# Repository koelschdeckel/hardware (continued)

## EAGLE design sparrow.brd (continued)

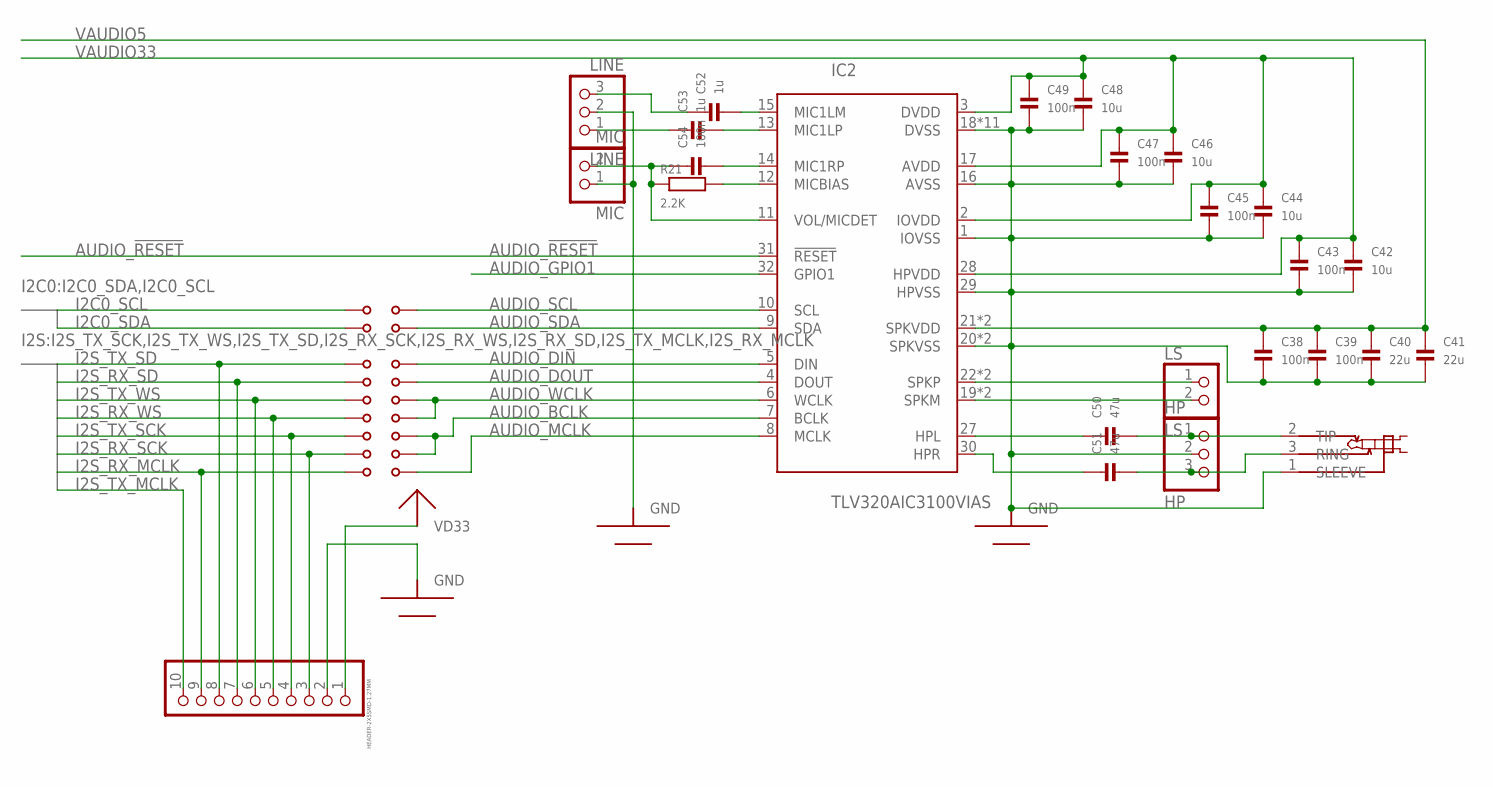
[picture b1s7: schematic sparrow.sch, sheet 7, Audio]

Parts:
A_SCL: JUMPERSOLDER_CLOSED; 0603_SOLDERJUMPER_CLOSED
A_SDA: JUMPERSOLDER_CLOSED; 0603_SOLDERJUMPER_CLOSED
C38, C39, C43, C45, C47, C49, C54: 100n; 0603
C40, C41: 22u; 0603
C42, C44, C46, C48: 10u; 0603
C50, C51: 47u; 0805
C52, C53: 1u; 0603
HEADPHONE: AUDIOJACK-STEREO-3PCUI_SJ_3523; CUI_SJ_3523_SMT
HP: HP; 1X03_ROUND
I2S: HEADER-2X5SMD-1.27MM; 2X05_SMT
IC2: TLV320AIC3100VIAS; QFN32-0.5-EP-VIAS
LINE: LINE; 1X03_ROUND
LS: LS; 1X02_ROUND
MCLK: JUMPERSOLDER_CLOSED; 0603_SOLDERJUMPER_CLOSED
MIC: MIC; 1X02_ROUND
R21: 2.2K; 0603
RX_SCK: JUMPERSOLDER_CLOSED; 0603_SOLDERJUMPER_CLOSED
RX_SD: JUMPERSOLDER_CLOSED; 0603_SOLDERJUMPER_CLOSED
RX_WS: JUMPERSOLDER_CLOSED; 0603_SOLDERJUMPER_CLOSED
TX_SCK: JUMPERSOLDER_CLOSED; 0603_SOLDERJUMPER_CLOSED
TX_SD: JUMPERSOLDER_CLOSED; 0603_SOLDERJUMPER_CLOSED
TX_WS: JUMPERSOLDER_CLOSED; 0603_SOLDERJUMPER_CLOSED

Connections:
AUDIO_!RESET: IC2.31 (!RESET); also elsewhere on the board
AUDIO_BCLK: IC2.7 (BCLK), RX_SCK.2, TX_SCK.2
AUDIO_DIN: IC2.5 (DIN), TX_SD.2
AUDIO_DOUT: IC2.4 (DOUT), RX_SD.2
AUDIO_GPIO1: IC2.32 (GPIO1)
AUDIO_MCLK: IC2.8 (MCLK), MCLK.2
AUDIO_SCL: A_SCL.2, IC2.10 (SCL)
AUDIO_SDA: A_SDA.2, IC2.9 (SDA)
AUDIO_WCLK: IC2.6 (WCLK), RX_WS.2, TX_WS.2
GND: C38.2, C39.2, C40.2, C41.2, C42.2, C43.2, C44.2, C45.2, C46.2, C47.2, C48.2, C49.2, HEADPHONE.1 (SLEEVE), HP.2, I2S.2, IC2.1 (IOVSS), IC2.16 (AVSS), IC2.18 (DVSS), IC2.20 (SPKVSS), IC2.25 (SPKVSS), IC2.29 (HPVSS), IC2.PAD (DVSS), IC2.VIA1 (DVSS), IC2.VIA2 (DVSS), IC2.VIA3 (DVSS), IC2.VIA4 (DVSS), IC2.VIA5 (DVSS), IC2.VIA6 (DVSS), IC2.VIA7 (DVSS), IC2.VIA8 (DVSS), IC2.VIA9 (DVSS), LINE.2, MIC.1; also elsewhere on the board
HPL: C50.1, IC2.27 (HPL)
HPR: C51.1, IC2.30 (HPR)
HP_L: C50.2, HEADPHONE.2 (TIP), HP.1
HP_R: C51.2, HEADPHONE.3 (RING), HP.3
I2C0_SCL: A_SCL.1; also elsewhere on the board
I2C0_SDA: A_SDA.1; also elsewhere on the board
I2S_RX_MCLK: I2S.9, MCLK.1; also elsewhere on the board
I2S_RX_SCK: I2S.3, RX_SCK.1; also elsewhere on the board
I2S_RX_SD: I2S.7, RX_SD.1; also elsewhere on the board
I2S_RX_WS: I2S.5, RX_WS.1; also elsewhere on the board
I2S_TX_MCLK: I2S.10; also elsewhere on the board
I2S_TX_SCK: I2S.4, TX_SCK.1; also elsewhere on the board
I2S_TX_SD: I2S.8, TX_SD.1; also elsewhere on the board
I2S_TX_WS: I2S.6, TX_WS.1; also elsewhere on the board
LINEIN1: C52.1, LINE.3
LINEIN2: C53.1, LINE.1
MIC1LM: C52.2, IC2.15 (MIC1LM)
MIC1LP: C53.2, IC2.13 (MIC1LP)
MIC1RP: C54.2, IC2.14 (MIC1RP)
MICBIAS: IC2.12 (MICBIAS), R21.2
unnamed: C54.1, IC2.11 (VOL/MICDET), MIC.2, R21.1
SPKM: IC2.19 (SPKM), IC2.23 (SPKM), LS.2
SPKP: IC2.22 (SPKP), IC2.26 (SPKP), LS.1
VAUDIO5: C38.1, C39.1, C40.1, C41.1, IC2.21 (SPKVDD), IC2.24 (SPKVDD); also elsewhere on the board
VAUDIO33: C42.1, C43.1, C44.1, C45.1, C46.1, C47.1, C48.1, C49.1, IC2.2 (IOVDD), IC2.3 (DVDD), IC2.17 (AVDD), IC2.28 (HPVDD); also elsewhere on the board
VD33: I2S.1; also elsewhere on the board

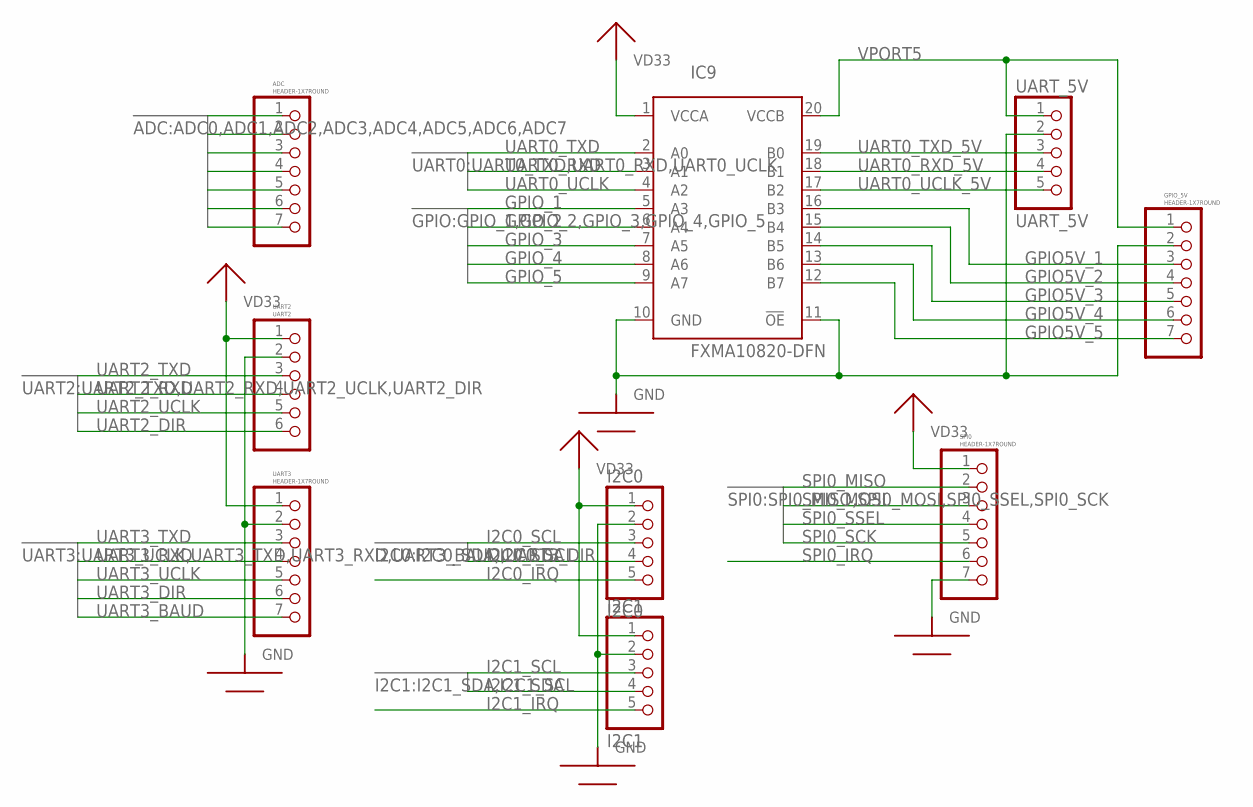
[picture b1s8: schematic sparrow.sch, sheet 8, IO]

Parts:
ADC: HEADER-1X7ROUND; 1X07_ROUND
GPIO_5V: HEADER-1X7ROUND; 1X07_ROUND
I2C0: I2C0; 1X05_ROUND
I2C1: I2C1; 1X05_ROUND
IC9: FXMA10820-DFN; FXMA108
SPI0: HEADER-1X7ROUND; 1X07_ROUND
UART2: UART2; 1X06_ROUND
UART3: HEADER-1X7ROUND; 1X07_ROUND
UART_5V: UART_5V; 1X05_ROUND

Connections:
ADC0: ADC.1; also elsewhere on the board
ADC1: ADC.2; also elsewhere on the board
ADC2: ADC.3; also elsewhere on the board
ADC3: ADC.4; also elsewhere on the board
ADC4: ADC.5; also elsewhere on the board
ADC5: ADC.6; also elsewhere on the board
ADC6: ADC.7; also elsewhere on the board
GND: GPIO_5V.2, I2C0.2, I2C1.2, IC9.10 (GND), IC9.11 (!OE), SPI0.7, UART2.2, UART3.2, UART_5V.2; also elsewhere on the board
GPIO5V_1: GPIO_5V.3, IC9.16 (B3)
GPIO5V_2: GPIO_5V.4, IC9.15 (B4)
GPIO5V_3: GPIO_5V.5, IC9.14 (B5)
GPIO5V_4: GPIO_5V.6, IC9.13 (B6)
GPIO5V_5: GPIO_5V.7, IC9.12 (B7)
GPIO_1: IC9.5 (A3); also elsewhere on the board
GPIO_2: IC9.6 (A4); also elsewhere on the board
GPIO_3: IC9.7 (A5); also elsewhere on the board
GPIO_4: IC9.8 (A6); also elsewhere on the board
GPIO_5: IC9.9 (A7); also elsewhere on the board
I2C0_IRQ: I2C0.5; also elsewhere on the board
I2C0_SCL: I2C0.3; also elsewhere on the board
I2C0_SDA: I2C0.4; also elsewhere on the board
I2C1_IRQ: I2C1.5; also elsewhere on the board
I2C1_SCL: I2C1.3; also elsewhere on the board
I2C1_SDA: I2C1.4; also elsewhere on the board
SPI0_IRQ: SPI0.6; also elsewhere on the board
SPI0_MISO: SPI0.2; also elsewhere on the board
SPI0_MOSI: SPI0.3; also elsewhere on the board
SPI0_SCK: SPI0.5; also elsewhere on the board
SPI0_SSEL: SPI0.4; also elsewhere on the board
UART0_RXD: IC9.3 (A1); also elsewhere on the board
UART0_RXD_5V: IC9.18 (B1), UART_5V.4
UART0_TXD: IC9.2 (A0); also elsewhere on the board
UART0_TXD_5V: IC9.19 (B0), UART_5V.3
UART0_UCLK: IC9.4 (A2); also elsewhere on the board
UART0_UCLK_5V: IC9.17 (B2), UART_5V.5
UART2_DIR: UART2.6; also elsewhere on the board
UART2_RXD: UART2.4; also elsewhere on the board
UART2_TXD: UART2.3; also elsewhere on the board
UART2_UCLK: UART2.5; also elsewhere on the board
UART3_BAUD: UART3.7; also elsewhere on the board
UART3_DIR: UART3.6; also elsewhere on the board
UART3_RXD: UART3.4; also elsewhere on the board
UART3_TXD: UART3.3; also elsewhere on the board
UART3_UCLK: UART3.5; also elsewhere on the board
VD33: I2C0.1, I2C1.1, IC9.1 (VCCA), SPI0.1, UART2.1, UART3.1; also elsewhere on the board
VPORT5: GPIO_5V.1, IC9.20 (VCCB), UART_5V.1; also elsewhere on the board

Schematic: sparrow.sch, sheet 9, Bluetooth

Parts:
ANT2: 2.4GHz 50Ω; 1206_MINIMELF_COMBO
BAL1: BALUNWLCSP; ST_BAL_WLCSP
C1: 1n; 0402
C61: 47n; 0402
C62, C63, C64: 100n; 0402
C66, C67: 12p; 0402
C68, C69: 9p; 0402
C72: 2.2n; 0402
MCU1: NRF51822QFN48; QFN48_EP
NRF_DEBUG: HEADER-2X5SMD-1.27MM; 2X05_SMT
R34: 100K; 0603
X3: 32768; 1206_MINIMELF_COMBO
X5: 16MHz; CRYSTAL25X20

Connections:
BT_ANT: ANT2.1, BAL1.SE (UNBAL)
BT_ANT1: BAL1.DIFF2 (BAL2), MCU1.31 (ANT1)
BT_ANT2: BAL1.DIFF1 (BAL1), MCU1.32 (ANT2)
BT_DEC1: C62.P$1, MCU1.39 (DEC1)
BT_DEC2: C61.P$1, MCU1.29 (DEC2)
BT_VDD_PA: BAL1.VCC (DC), C72.P$2, MCU1.30 (VDD_PA)
BT_XC1: C67.P$1, MCU1.37 (XC1), X5.1
BT_XC2: C66.P$1, MCU1.38 (XC2), X5.3 (2)
BT_XL1: C69.P$2, MCU1.46 (P0.27), X3.1
BT_XL2: C68.P$2, MCU1.45 (P0.26), X3.2
GND: BAL1.GND, C1.P$2, C61.P$2, C62.P$2, C63.P$2, C64.P$2, C66.P$2, C67.P$2, C68.P$1, C69.P$1, C72.P$1, MCU1.13 (VSS), MCU1.33 (VSS), MCU1.34 (VSS), MCU1.PAD (VSS), NRF_DEBUG.3, NRF_DEBUG.5, NRF_DEBUG.7, NRF_DEBUG.9, R34.1, X5.2 (GND), X5.4 (GND); also elsewhere on the board
NRF_SWDCLK: MCU1.24 (SWDCLK), NRF_DEBUG.4, R34.2; also elsewhere on the board
NRF_SWDIO: MCU1.23 (SWDIO/NRESET), NRF_DEBUG.2; also elsewhere on the board
UART1_CTS: MCU1.7 (P0.03); also elsewhere on the board
UART1_RTS: MCU1.6 (P0.02); also elsewhere on the board
UART1_RXD: MCU1.5 (P0.01); also elsewhere on the board
UART1_TXD: MCU1.4 (P0.00); also elsewhere on the board
VD33: C1.P$1, C63.P$1, C64.P$1, MCU1.1 (VDD), MCU1.12 (VDD), MCU1.35 (AVDD), MCU1.36 (AVDD), NRF_DEBUG.1; also elsewhere on the board

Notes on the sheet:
Note: R34 only needed for first revision of NRF51822. DNP for Rev. 2 and up.

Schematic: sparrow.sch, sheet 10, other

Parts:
LOGO2, LOGO3, LOGO4: LOGOKRONE; LOGO-KRONE

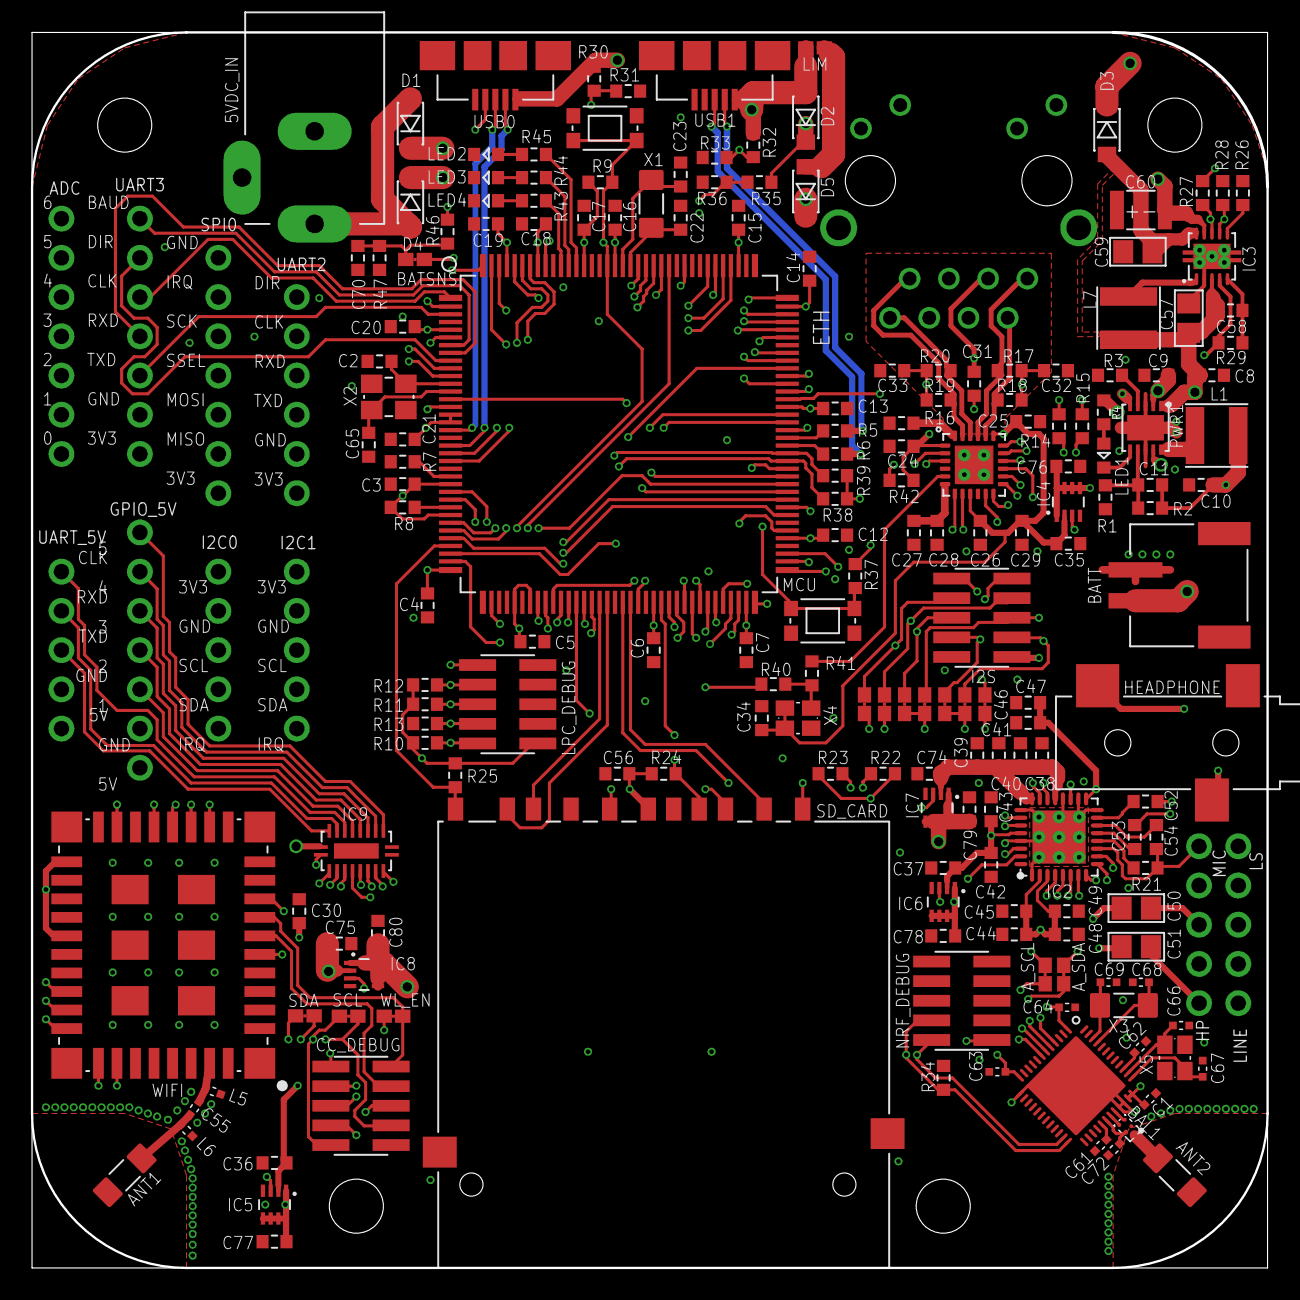
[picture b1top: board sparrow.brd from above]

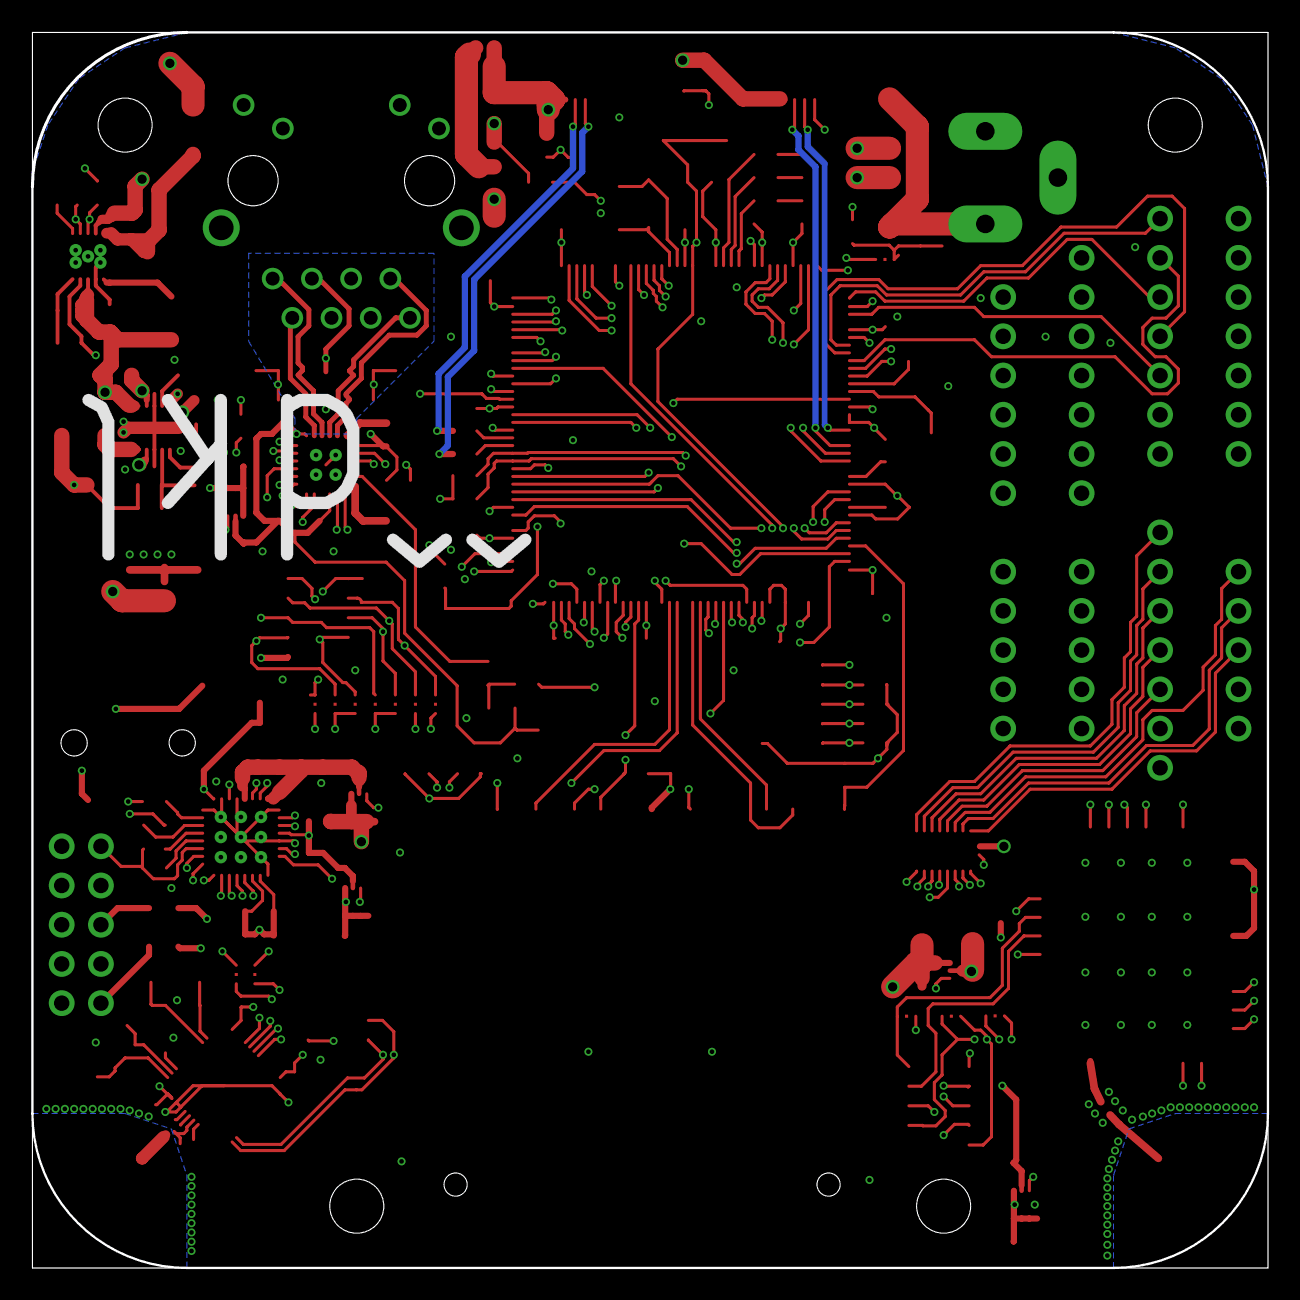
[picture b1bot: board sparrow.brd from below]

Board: 4 copper layers, 80.0 x 80.0 mm, 201 parts (3 on the bottom side), 193 nets.

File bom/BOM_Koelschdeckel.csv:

,BOM #,# Sparrow,Parts sparrow,Type,Value,Shape,Manuf,Model,Alt,Mouser #,DK #
,,,,,,,,,,,
Resistors,,,,,,,,,,,
,1,4,"R5, R6, R40, R41",Resistor,33Ω 1%,0603,Samsung,RC1608F330CS,"Vishay CRCW060333R0FKEA, Rohm MCR03ERTF33R0",71-CRCW0603-33-E3,1276-4524-1-ND
,2,4,"R17, R18, R19, R20",Resistor,49.9Ω 1%,0603,Samsung,RC1608F49R9CS,Vishay CRCW060349R9FKEA,71-CRCW0603-49.9-E3,1276-3505-1-ND
,3,2,"R14, R15",Resistor,330Ω,0603,Samsung,RC1608J331CS,"Yageo RC0603JR-07330RL, Yageo AF0603FR-07330RL, Vishay CRCW0603330RFKEA ",71-CRCW0603-330-E3,311-330GRCT-ND
,4,1,R3,Resistor,806Ω,0603,Yageo,RC0603FR-07806RL,KOA RK73H1JTTD8060F,660-RK73H1JTTD8060F,311-806HRCT-ND
,5,4,"R4, R43, R44, R45",Resistor,1K,0603,Samsung,RC1608J102CS,"Vishay CRCW06031K00FKEA, KOA RK73H1JTTD1001F",660-RK73H1JTTD1001F,1276-5062-1-ND
,6,5,"R21, R22, R23, R38, R39",Resistor,2.2K,0603,Samsung,RC1608J222CS,"KOA RK73H1JTTD2201F, Vishay CRCW06032K20FKEA, Yageo RC0603JR-072K2L",660-RK73H1JTTD2201F,1276-5070-1-ND
,7,9,"R30, R32, R42, R8, R9, R10, R11, R12, R13",Resistor,10K,0603,Samsung,RC1608J103CS,"Yageo RC0603JR-0710KL, Voshay CRCW060310K0FKEA, KOA RK73H1JTTD1002F",660-RK73H1JTTD1002F,1276-5086-1-ND
,8,1,R7,Resistor,12K 1%,0603,Samsung,RC1608F123CS,"Rohm MCR03ERTF1202, KOA RK73H1JTTD1212F, Vishay CRCW060312K1FKEA",660-RK73H1JTTD1212F,1276-4750-1-ND
,9,1,R16,Resistor,12.1K 1%,0603,Samsung,RC1608F1212CS,"KOA RK73H1JTTD1212F, Vishay CRCW060312K1FKEA, Stackpole RMCF0603FT12K1",660-RK73H1JTTD1212F,1276-4751-1-ND
,10,1,R26,Resistor,40.2K,0603,Samsung,RC1608F4022CS,"Yageo RC0603FR-0740K2L, KOA RK73H1JTTD4022F, Vishay CRCW060340K2FKEB",660-RK73H1JTTD4022F,1276-4800-1-ND
,11,11,"R24, R25, R27, R28, R29, R31, R33, R34, R35, R36, R37",Resistor,100K,0603,Samsung,RC1608J104CS,"Yageo RC0603JR-07100KL, Vishay CRCW0603100KFKEA, KOA RK73H1JTTD1003F",660-RK73H1JTTD1003F,1276-5110-1-ND
,12,3,"R1, R46, R47",Resistor,768K,0603,Yageo,RC0603FR-07768KL,"KOA RK73H1JTTD7683F, Rohm MCR03ERTF7683, Vishay CRCW0603768KFKEA",660-RK73H1JTTD7683F,311-768KHRCT-ND
,13,1,R2,Resistor,2.4M,0603,Samsung,RC1608J245CS,"KOA RK73B1JTTD245J, Vishay CRCW06032M40JNEA, Yageo RC0603JR-072M4L",660-RK73B1JTTD245J,1276-5143-1-ND
Capacitors,,,,,,,,,,,
,14,1,C55,Capacitor,2.2p,0402,Samsung,CL05C2R2CB5NNNC,Johanson 500R07S2R2DV4T,609-500R07S2R2DV4T,1276-1271-1-ND
,15,2,"C68, C69",Capacitor,9p,0402,Samsung,CL05C090DB5NNNC,Murata GRM1555C1H9R0CA01D,81-GRM1555C1H9R0CA1D,1276-1617-1-ND
,16,,,Capacitor,9p,0603,Samsung,CL10C090DB8NNNC,TDK C1608C0G1H090C080AA,810-C1608C0G1H090C,1276-2143-1-ND
,17,1,C11,Capacitor,10p 5%,0603,Samsung,CL10C100JB8NCNC,Vishay VJ0603A100JXACW1BC,77-VJ0603A100JXACBC,1276-2154-1-ND
,18,2,"C66, C67",Capacitor,12p,0402,Samsung,CL05C120JB5NNNC,Johanson 500R07S120KV4T,609-500R07S120KV4T,1276-1178-1-ND 
,19,4,"C2, C22, C23, C65",Capacitor,18p 5%,0603,Samsung,CL10C180JC8NNNC,Vishay VJ0603A180JXACW1BC,77-VJ0603A180JXACBC,1276-2210-1-ND
,20,1,C28,Capacitor,470p 5%,0603,Samsung,CL10C471JB8NCNC,Vishay VJ0603A471JXXCW1BC,77-VJ0603A471JXXCBC,1276-2302-1-ND
,21,1,C1,Capacitor,1n,0402,Samsung,CL05B102KB5NCNC,KOA X7R0402HTTP102K,660-X7R0402HTTP102K,1276-1492-1-ND
,22,1,C72,Capacitor,2.2n,0402,Samsung,CL05B222KB5NNNC,Vishay VJ0402Y222KXJCW1BC,77-VJ0402Y222KXJCBC,1276-1054-1-ND
,23,3,"C24, C25, C26",Capacitor,10n, ,Samsung,CL10B103KB8NCNC,Vishay VJ0603Y103KXAAC,77-VJ0603Y103KXAAC,1276-1921-1-ND
,24,1,C61,Capacitor,47n,0402,Samsung,CL05B473KP5NNNC,Vishay VJ0402Y473KXQCW1BC,77-VJ0402Y473KXQCBC,1276-1573-1-ND
,25,3,"C62, C63, C64",Capacitor,100n,0402,Samsung,CL05A104KP5NNNC,Vishay VJ0402G104MXQPW1BC,77-VJ0402G104MXQPBC,1276-1022-1-ND
,26,34,"C3, C4, C5, C6, C7, C12, C13, C14, C15, C16, C17, C18. C19, C20, C21, C30, C31, C32, C33, C34, C35, C36, C37. C38, C39, C43, C45, C47, C49, C54, C58, C70, C74, C75",Capacitor,100n,0603,Samsung,CL10B104KO8NNNC,Vishay VJ0603Y104JXJPW1BC,77-VJ0603Y104JXJPBC,1276-1005-1-ND
,27,9,"C27, C52, C53, C56, C76, C77, C78, C79, C80",Capacitor,1u,0603,Samsung,CL10B105KP8NNNC,AVX 0603YD105KAT2A,581-0603YD105K,1276-1946-1-ND
,28,3,"C8, C9, C10",Capacitor,4.7u,0603,Samsung,CL10B475KQ8NQNC,Murata GRM188R60J475ME19D,81-GRM188R60J475ME9D,1276-2087-1-ND
,29,5,"C29, C42, C44, C46, C48",Capacitor,10u,0603,Samsung,CL10A106MQ8NNNC,AVX 06036D106MAT2A,581-06036D106MAT2A,1276-1119-1-ND
,30,2,"C40, C41",Capacitor,22u 6.3V,0603,Samsung,CL10A226MQ8NRNC,"Murata GRM188R60J226MEA0D, TDK C1608X5R0J226M080AC",810-C1608X5R0J226M,1276-1193-1-ND
,31,2,"C57, C59",Capacitor,22u 10V,0805,Samsung,CL21A226MPQNNNE,TDK C2012X5R1A226M125AB,810-C2012X5R1A226M-3,1276-2910-1-ND
,32,2,"C50, C51",Capacitor,47u 6.3V,0805,Samsung,CL21A476MQCLRNC,Taiyo Yuden JMK212BJ476MG-T,963-JMK212BJ476MG-T,1276-2420-1-ND
,33,1,C60,Capacitor,150u 10V,1210_POL,AVX,TLNT157M010R1500,AVX TLJB157M010R0500,581-TLNT157M010R,478-3349-1-ND
Inductors,,,,,,,,,,,
,34,1,L5,Inductor,2.2n,0402,Taiyo Yuden,HK10052N2S-T,"Taiyo Yuden HK10052N2S-T, Panasonic ELJ-RF2N2ZFB, TDK MLG1005S2N2S",963-HK10052N2S-T,587-1503-1-ND
,35,1,L7,Inductor,"2.2u 2.2Arms, 3A sat",40x40,Laird,TYS40302R2N-10,"Bourns SRN4018-2R2M, Taiyo Yuden NRS4018T2R2MDGJ",963-NRS4018T2R2MDGJ,240-2697-1-ND
,36,1,L1,Inductor,10u 1A,40x40,Taiyo Yuden,NRS4018T100MDGJ,,963-NRS4018T100MDGJ,587-2886-1-ND
Diodes,,,,,,,,,,,
,37,5,"D1, D2, D3, D4, D5",Diode,2A 30V Schottky,SOD123/ SOD123FL,ON Semi,MBR230LSFT1,Comchip CDBMT240-HF,863-MBR230LSFT1G,MBR230LSFT1GOSCT-ND
LEDs,,,,,,,,,,,
,38,4,"LED1, LED2, LED3, LED4",LED,"any color, 100mcd min",0603_POL,Vishay,VLMY1300-GS08 (yellow),Osram LS Q976-NR-1,78-VLMY1300-GS08,475-2512-1-ND
ICs,,,,,,,,,,,
,39,1,IC1,IC,LAN8720A,QFN24-0.5,SMSC/Microchip,LAN8720A/ LAN8720AI,,886-LAN8720A-CP,LAN8720A-CP-CT-ND
,40,1,IC2,IC,TLV320AIC3100,QFN32-0.5,TI,TLV320AIC3100IRHBR/T,,595-V320AIC3100IRHBT,296-25494-1-ND
,41,1,IC3,IC,TPS2500,SON10-0.5,TI,TPS2500DRCT,,595-TPS2500DRCT,296-32462-1-ND
,42,5,"IC4, IC5, IC6, IC7, IC8",IC,AAT4280A,SC70JW-8,Skyworks,AAT4280A,,873-AAT4280AIJS-2-T1,863-1480-1-ND
,43,1,IC9,IC,FXMA108,DFN20,Fairchild,FXMA108,,512-FXMA108BQX,FXMA108BQXFSCT-ND
,44,1,MCU,IC,NXP1837,QFP144-0.5,NXP,LPC1837JBD144E,,771-LPC1837JBD144E,LPC1837JBD144E-ND
,45,1,MCU1,IC,NRF51822,QFN48-0.4,Nordic Semi,NRF51822QFAA,,949-NRF51822-QFAA-R7,
,46,,,IC,PN532,QFN40,NXP,PN5321A3HN/C106;55,,771-PN5321A3HNC106,568-8600-ND
,47,1,PWR1,IC,LTC4080,DFN10,Linear,LTC4080,LTC4081,,LTC4081EDD#PBF-ND
Modules,,,,,,,,,,,
,48,1,WIFI,Module,CC3000,,TI,CC3000MOD,,595-CC3000MOD,296-35512-1-ND
Clocks,,,,,,,,,,,
,49,2,"X1, X3",Crystal,32.768KHz 12.5pF,1206,Abracon,ABS07,"TXC 9HT10-32.768KAZF-T, Citizen CM315D32768DZFT",717-9HT10-32.768KAZF,300-8814-1-ND
,50,1,X2,Crystal,12MHz 10pF 40ppm,3.2 x 2.5,AVX,CX3225GB12000P0HPQCC,ABM8G-12.000MHZ-4Y-T3,581-CX3225GB12PHPQCC,535-10901-1-ND
,51,1,X5,Crystal,16MHz 8pF 40ppm,2.5 x 2.0,AVX,CX2520DB16000D0GEJCC,,581-CX2520DB16DGEJCC,1253-1122-1-ND
,52,,,Crystal,27.12MHz 10pF 20ppm,5 x 3.2,TXC,7B-27.120MEEQ-T,,,887-1309-1-ND
,53,1,X4,Oscillator,50MHz,2.5 x 2.0,SiLabs,501AAA50M0000DAG,SITime SiT8103AI-13-33E-50.00000X,788-8103I-333E50X,336-2981-ND
RF,,,,,,,,,,,
,54,2,"ANT1, ANT2",Antenna,2.4GHz,1206,Abracon,AMCA31-2R450G-S1F,,815-CA312R450GS1FT,535-12386-1-ND
,55,1,BAL1,Balun,for NRF51822,WLCSP5,ST,BALF-NRF01D3,BAL-NRF01D3 (worse),511-BAL-NRF01D3,497-13637-1-ND
Mechanical,,,,,,,,,,,
,56,2,"!PGM, RESET",Button,CK-KMR2,,CK,KMR2xx,,611-KMR211G-LFS,CKN10272CT-ND
,57,1,5VDC_IN,Connector,Barrel 5.5/2.1 2A,,CUI,PJ 102AH,,,CP-102AH-ND
,58,1,BATT,Connector,2mm LiPo/Li-Ion,,JST,PH-H,,,455-1749-1-ND 
,59,1,ETH,Connector,RJ45-Mag-LEDs,,WIZnet,RB1-125BAG1A,,950-RB1-125BAG1A,1278-1011-ND
,60,1,HEADPHONE,Connector,3.5mm stereo,,CUI,SJ 3523,Switchcraft 35RASMT2BHNTRX,502-35RASMT2BHNTRX,CP-3523SJCT-ND
,61,1,SD_CARD,Connector,SD card holder,,Amphenol,101_00313,,523-101-00313-68-02,
,62,1,USB1,Connector,Micro USB-B,,FCI,10104110-0001LF,,649-10104110-0001LF,
,63,1,USB0,Connector,Micro USB-AB,,FCI,10104111-0001LF,,649-10104111-0001LF,
,,,,,,,,,,,
,,,,,,,,,,,
,,,ARM DEBUGs,,,,,,,,

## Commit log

2014-01-14 initial version
2014-01-28 Further work
2014-03-12 positioned and connected headers
2014-03-12 layout refinements
2014-03-14 basic routing finished
2014-03-14 Silkscreen fixed
2014-03-25 power routing, added LEDs, several last-minute improvements
2014-03-25 moved artwork
2014-04-14 gitignore
2014-04-16 renamed library everykey
2014-04-16 approved sup/out erc warning
2014-04-16 phy capacitors
2014-04-16 moved caps
2014-04-16 Added battery sensing
2014-04-17 Final impedance touchup
2014-04-17 Last library update, DRC fixes
2014-05-04 Updated values
2014-05-05 value tuning
2015-04-02 Fine tuning
2015-04-02 added pdf renamed to koelschdeckel
2015-04-02 README
2015-04-02 added BOM
2015-04-02 moved bom to own directory
